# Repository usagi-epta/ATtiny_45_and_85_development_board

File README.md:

ATtiny 45 and 85 Development Board
==================================
Copyright 2011 Design Tech Industries (DTI)

DTI email: <jameskun89@rocketmail.com>

The **ATtiny 45 and 85 Development Board** is a development board for the ATtiny 45 and 85 microcontroller.

Features:

 * All µC pins broken out
 * Power LED
 * Reset switch
 * ISP headers 
 * Open Source; OSHW compliant
 * Design files freely available

In this repository you will find the gerber files for BatchPCB (http://batchpcb.com) and DorkbotPDX (http://dorkbotpdx.org/wiki/pcb_order),
along with project (.pro), board (.brd) and schematic (.sch) files for the board in the 'EAGLE and 'KiCad' folders.

You can also find this design on BatchPCB ready to add to your cart: http://batchpcb.com/index.php/Products/73630

**This board will be under continual change and versions may not work the way they are supposed to. You have been warned**

INSTALLATION
------------
**EAGLE**
The design is saved as an EAGLE project. EAGLE PCB design software is available from www.cadsoftusa.com 
free for non-commercial use and can be installed on Windows and Mac, with Linux support through WINE. 
To use this project download it and place the directory containing these files into the "eagle" directory 
on your computer. Then open EAGLE and navigate to Projects -> eagle -> ATtiny_45_and_85_development_board.

**KiCad**
KiCad EDA Suite is an Open Source alternative to EAGLE. It is available on Windows and Linux and can be installed 
on Mac. It is available from http://kicad.sourceforge.net and works in a similar way to EAGLE. You will find project 
files for KiCad in the aptly named folder in this repository. To use this project download it and place the directory 
containing these files into a folder of your choice. Then open KiCad and navigate to File -> Open -> 
'FOLDER_OF_YOUR_CHOICE' -> ATtiny_45_and_85_development_board.pro

BILL OF MATERIALS
-----------------

 * 1 x ATtiny 45/85 µC (http://littlebirdelectronics.com/products/avr-8-pin-20mhz-8k-4ad-attiny85)
 * 1 x 8-pin DIP socket (http://littlebirdelectronics.com/products/dip-sockets-solder-tail-8pin)
 * 2 x Female Header - 1x4-pin, Straight (http://littlebirdelectronics.com/products/0100-254-mm-female-header-1x4-pin-straight)
 * 1 x Break Away Header - Right Angle (http://littlebirdelectronics.com/products/break-away-headers-right-angle)
 * 1 x 5mm Green LED (http://littlebirdelectronics.com/products/basic-led-5mm-green)
 * 1 x 10uF Capacitor (http://littlebirdelectronics.com/products/electrolytic-decoupling-capacitors-10uf-25v)
 * 1 x 0.1uF Ceramic Capacitor (http://littlebirdelectronics.com/products/capacitor-ceramic-0-1uf)
 * 1 x 10K 1/4 resistor & 490K 1/4 resistor (can swap for 470K) (http://littlebirdelectronics.com/products/14-watt-carbon-film-resistors-300-pieces)
 * 1 x Mini Push Button Switch (http://littlebirdelectronics.com/products/mini-push-button-switch)

DISTRIBUTION
------------
The specific terms of distribution of this project are governed by the license referenced below.

LICENSE
-------
> This work is licensed under the Creative Commons Attribution-ShareAlike License.  
> 
> To view a copy of this license, visit:
> 
>   http://creativecommons.org/licenses/by-sa/3.0/  
>   http://creativecommons.org/licenses/by-sa/3.0/legalcode
> 
> or send a letter to
> 
>   Creative Commons  
>   171 Second Street, Suite 300  
>   San Francisco  
>   California, 94105  
>   USA

The "license" folder within this repository also contains copies of the
license(s) referenced above.

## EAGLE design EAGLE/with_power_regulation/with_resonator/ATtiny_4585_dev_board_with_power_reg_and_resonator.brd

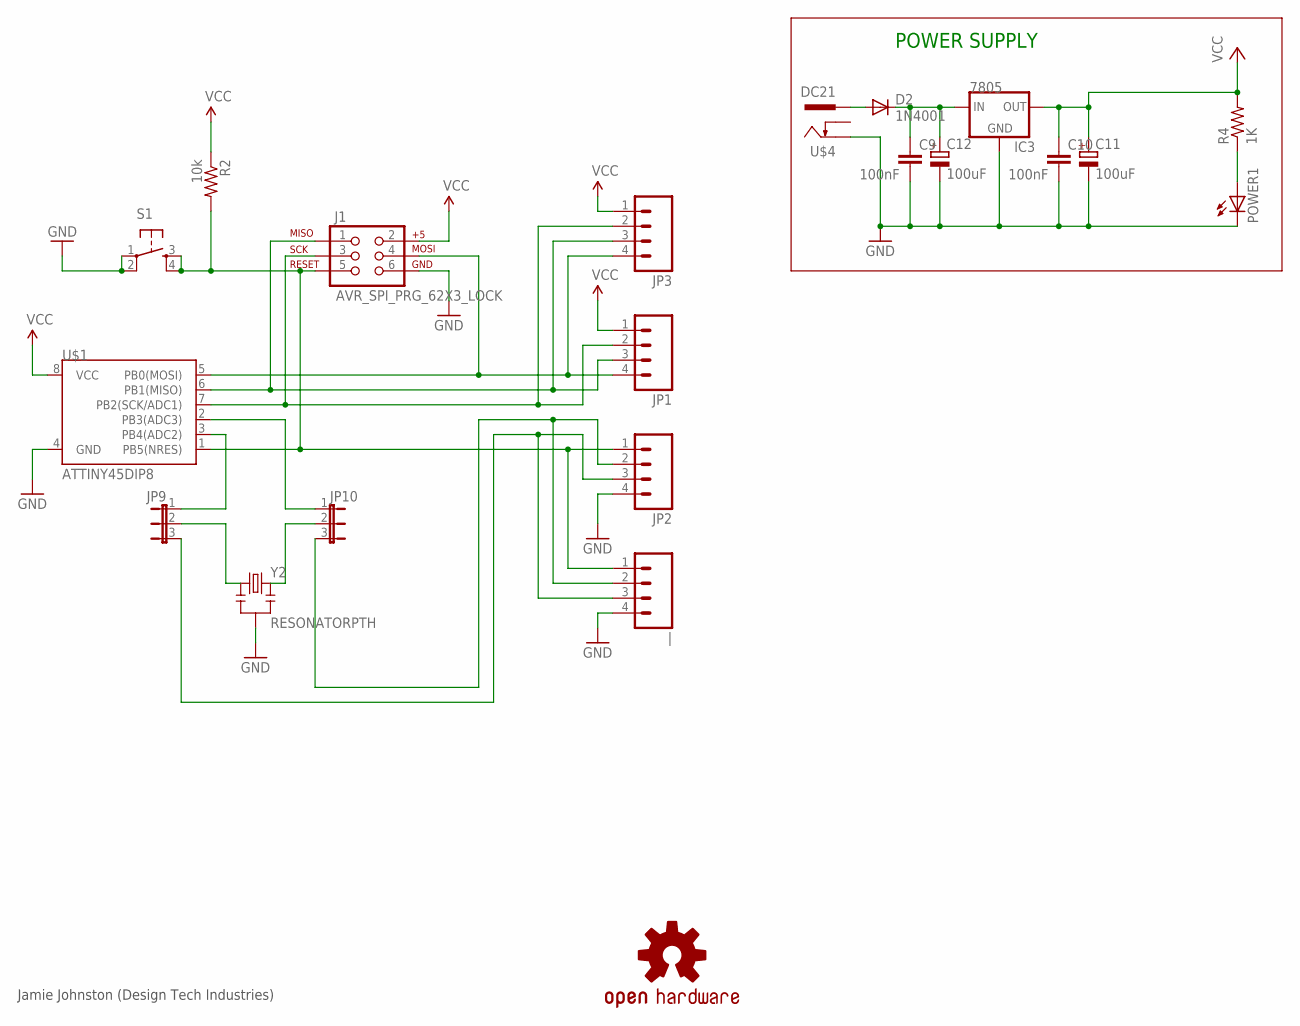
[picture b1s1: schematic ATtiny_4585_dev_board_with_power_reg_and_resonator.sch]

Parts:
C9, C10: 100nF; C050-030X075
C11, C12: 100uF; E2,5-6
D2: 1N4001; DO41-10
IC3: 7805; TO220-IGO
J1: AVR_SPI_PRG_62X3_LOCK; 2X3_LOCK
JP1, JP2, JP3: M04LOCK; 1X04_LOCK
JP9, JP10: JP2E; JP2
POWER1: LED3MM
R2: 10k; AXIAL-0.4
R4: 1K; 0207/2V
S1: TAC_SWITCHPTH; TACTILE-PTH
U$1: ATTINY45DIP8; DIP08
U$3: OSHW-LOGOM; OSHW-LOGO-M
U$4: DC21; DCSKT
Y2: RESONATORPTH; RESONATOR-PTH
|: M04LOCK; 1X04_LOCK

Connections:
GND: C9.2, C10.2, C11.-, C12.-, IC3.GND, J1.6, JP2.4, POWER1.K (C), S1.1, S1.2, U$1.4 (GND), U$4.2, Y2.2, |.4
unnamed: JP9.1, U$1.3 (PB4(ADC2))
unnamed: J1.4, JP1.4, JP3.4, U$1.5 (PB0(MOSI))
unnamed: J1.5, JP2.1, R2.P$2 (2), S1.3, S1.4, U$1.1 (PB5(NRES)), |.1
unnamed: JP10.1, U$1.2 (PB3(ADC3))
unnamed: J1.1, JP1.3, JP3.3, U$1.6 (PB1(MISO))
unnamed: J1.3, JP1.2, JP3.2, U$1.7 (PB2(SCK/ADC1))
unnamed: JP2.2, JP10.3, |.2
unnamed: JP2.3, JP9.3, |.3
unnamed: POWER1.A, R4.1
unnamed: JP9.2, Y2.1
unnamed: JP10.2, Y2.3
VCC: C10.1, C11.+, IC3.OUT, J1.2, JP1.1, JP3.1, R2.P$1 (1), R4.2, U$1.8 (VCC)
VIN: D2.A, U$4.1
VIN_SAFE: C9.1, C12.+, D2.C, IC3.IN

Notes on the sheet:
POWER SUPPLY
Jamie Johnston (Design Tech Industries)

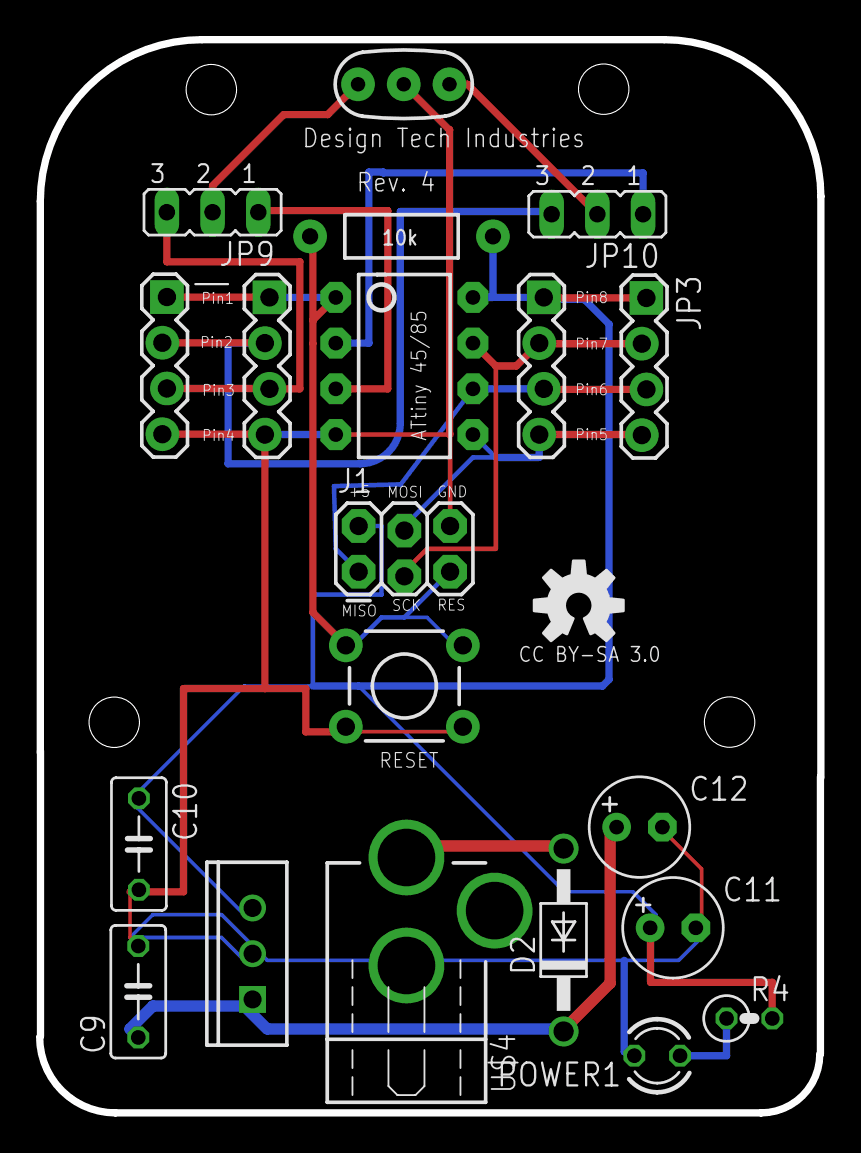
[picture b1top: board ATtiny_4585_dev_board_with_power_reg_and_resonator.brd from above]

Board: 2 copper layers, 43.4 x 59.6 mm, 21 parts (0 on the bottom side), 15 nets.

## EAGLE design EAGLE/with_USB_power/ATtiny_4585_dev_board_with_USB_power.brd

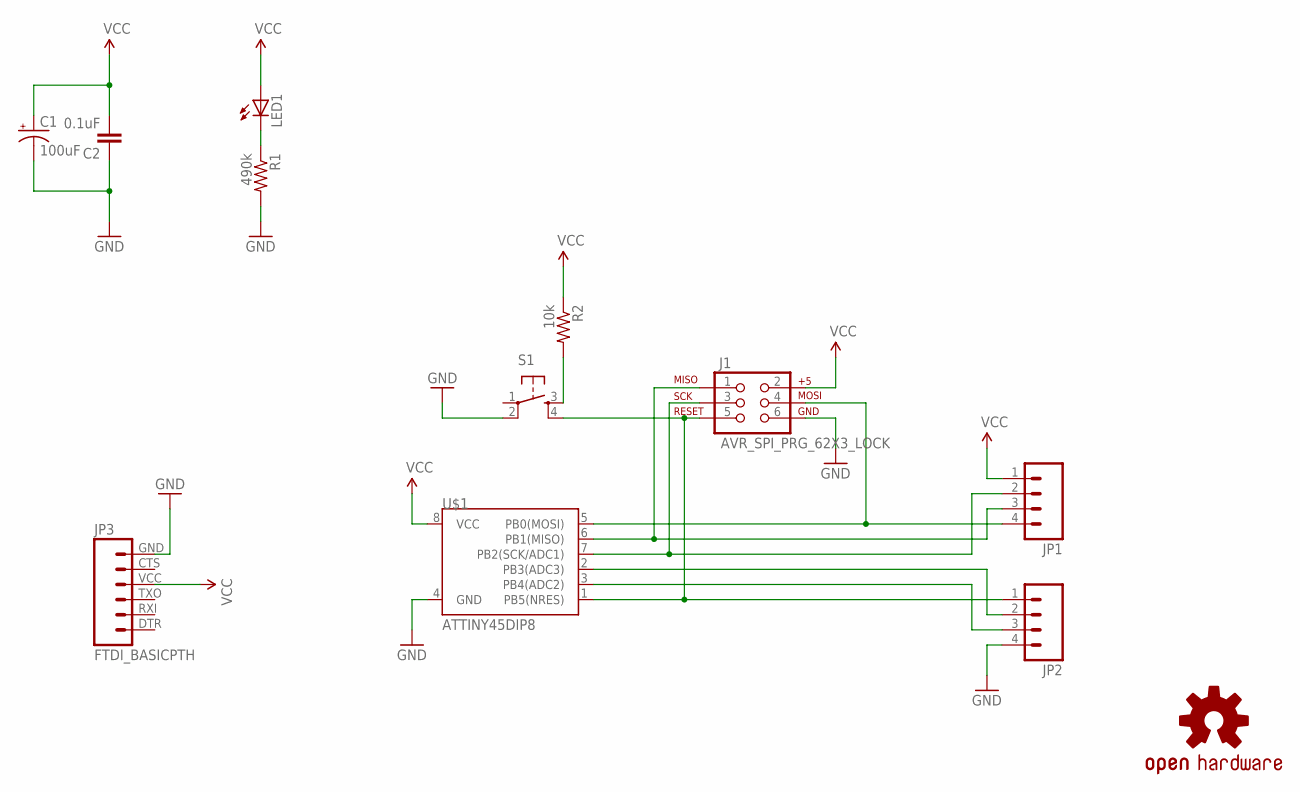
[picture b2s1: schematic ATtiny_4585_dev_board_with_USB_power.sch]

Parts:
C1: 100uF; CPOL-RADIAL-100UF-25V
C2: 0.1uF; CAP-PTH-5MM
J1: AVR_SPI_PRG_62X3_LOCK; 2X3_LOCK
JP1, JP2: M04LOCK; 1X04_LOCK
JP3: FTDI_BASICPTH; FTDI_BASIC
LED1: LED5MM
R1: 490k; AXIAL-0.4
R2: 10k; AXIAL-0.4
S1: TAC_SWITCHPTH; TACTILE-PTH
U$1: ATTINY45DIP8; DIP08
U$2: OSHW-LOGOS; OSHW-LOGO-S

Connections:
GND: C1.2 (-), C2.1, J1.6, JP2.4, JP3.GND (6), R1.P$2 (2), S1.2, U$1.4 (GND)
unnamed: LED1.K (C), R1.P$1 (1)
unnamed: J1.4, JP1.4, U$1.5 (PB0(MOSI))
unnamed: J1.5, JP2.1, S1.4, U$1.1 (PB5(NRES))
unnamed: J1.1, JP1.3, U$1.6 (PB1(MISO))
unnamed: J1.3, JP1.2, U$1.7 (PB2(SCK/ADC1))
unnamed: R2.P$2 (2), S1.3
unnamed: JP2.2, U$1.2 (PB3(ADC3))
unnamed: JP2.3, U$1.3 (PB4(ADC2))
VCC: C1.1 (+), C2.2, J1.2, JP1.1, JP3.VCC (4), LED1.A, R2.P$1 (1), U$1.8 (VCC)

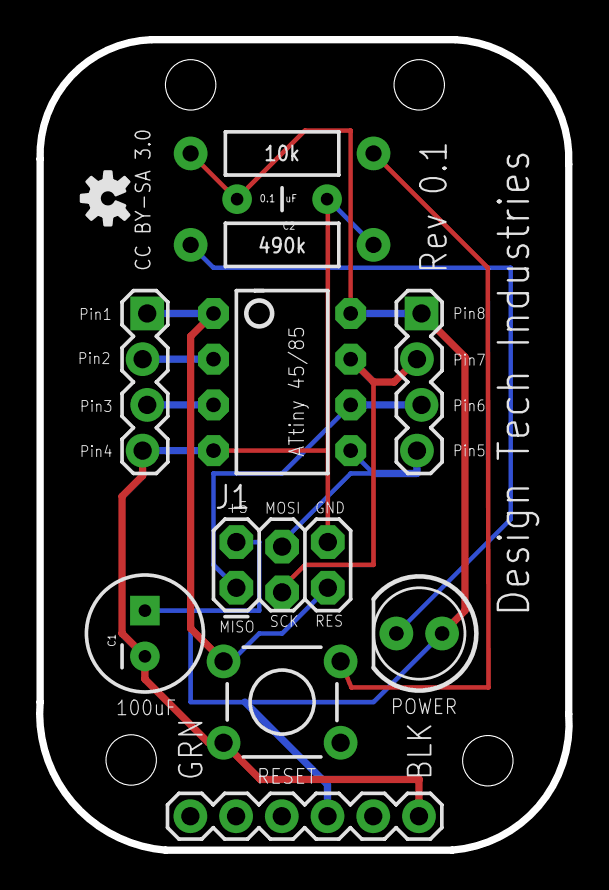
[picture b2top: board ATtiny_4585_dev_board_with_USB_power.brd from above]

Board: 2 copper layers, 29.4 x 45.0 mm, 12 parts (0 on the bottom side), 10 nets.

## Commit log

2011-12-01 Initial commit of files.
2011-12-01 Commit of newly created files, including design with power supply.
2011-12-03 Commit of new files, including images of the board.
2011-12-13 Upgraded to EAGLE 6 and resaved files in new XML format.
2011-12-29 Added a Bill of Materials. Changes will be made once prototypes are made.
2011-12-29 Minor edit.
2012-07-23 Added 5v power regulation and power jack. Included extra headers, breaking out the pins to the ATtiny45/85 chip to the bottom of board to allow unused pins to be used while 'shield' is in use.
2012-07-23 General folder clean up.
2012-07-23 Update of design files. Minor changes to thermocouple solder pads. New board images in 'docs' folder.
2012-07-24 Commit of revision 4 of board. This version now includes a resonator and selector jumpers, so as to allow you to choose if the resonator is needed or whether the pins are needed for something else.

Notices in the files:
EAGLE/with_USB_power/ATtiny_4585_dev_board_with_USB_power.brd:
CC BY-SA 3.0
parts and their libraries:
SparkFun-Aesthetics: Licensing: CC v3.0 Share-Alike You are welcome to use this library for commercial purposes.
